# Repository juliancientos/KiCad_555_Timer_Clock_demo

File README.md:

# 555 Timer Clock – 2‑Layer PCB Demonstration (KiCad)

## Overview
This project is a **beginner‑level demonstration of a 2‑layer PCB design** created in **KiCad**, using a simple **555 Timer Clock circuit** as the example.

The primary goal of this project is **to teach and practice basic 2‑layer PCB concepts**, not to create an optimized or production‑ready design. It is intended for students, hobbyists, and beginners learning PCB layout.

---

## Learning Objectives
This project demonstrates:
- Basic **2‑layer PCB layout** (Top & Bottom copper)
- Proper use of **ground planes**
- Via usage between layers
- Simple component placement and routing
- KiCad schematic → PCB workflow

---

## Circuit Description
The circuit is based on a **NE555 Timer IC** configured in **astable mode** to generate a continuous clock signal.

The timing frequency is set by two resistors and one capacitor:

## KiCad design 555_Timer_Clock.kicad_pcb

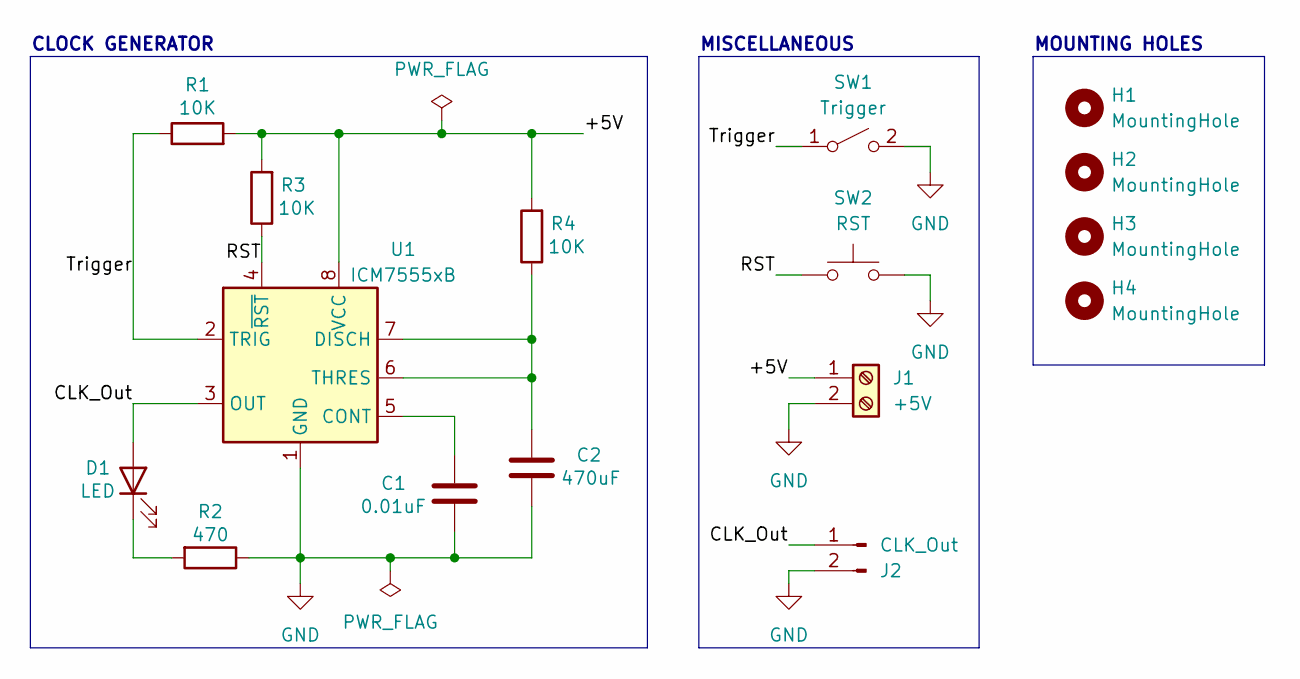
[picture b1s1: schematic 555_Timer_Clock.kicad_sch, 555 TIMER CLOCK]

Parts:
C1: 0.01uF; C_Disc_D3.8mm_W2.6mm_P2.50mm
C2: 470uF; CP_Elec_5x5.4
D1: LED; LED_D5.0mm
H1, H2, H3, H4: MountingHole; MountingHole_2.2mm_M2
J1: +5V; Terminal_Block_5mm
J2: CLK_Out; PinHeader_1x02_P2.54mm_Vertical
R1, R3, R4: 10K; R_1206_3216Metric_Pad1.30x1.75mm_HandSolder
R2: 470; R_1206_3216Metric_Pad1.30x1.75mm_HandSolder
SW1: Trigger; slide_switch_2.54mm
SW2: RST; tact_switch_5mm
U1: ICM7555xB; SOIC-8_3.9x4.9mm_P1.27mm

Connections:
/+5V: J1.1, R1.2, R3.2, R4.2, U1.8 (VCC)
/CLK_Out: D1.2 (A), J2.1, U1.3 (OUT)
/RST: R3.1, SW2.1, U1.4 (~RST)
/Trigger: R1.1, SW1.1 (A), U1.2 (TRIG)
GND: C1.2, C2.2, J1.2, J2.2, R2.1, SW1.2 (B), SW2.2, U1.1 (GND)
unnamed: D1.1 (K), R2.2
unnamed: C1.1, U1.5 (CONT)
unnamed: C2.1, R4.1, U1.6 (THRES), U1.7 (DISCH)

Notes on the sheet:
CLOCK GENERATOR
MOUNTING HOLES
MISCELLANEOUS

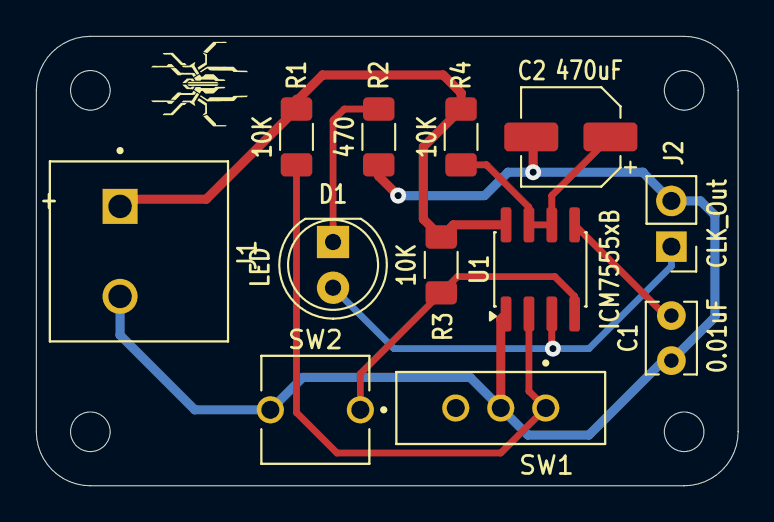
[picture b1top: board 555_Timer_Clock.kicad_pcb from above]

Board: 2 copper layers, 39.0 x 25.0 mm, 16 parts (0 on the bottom side), 8 nets.

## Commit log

2026-04-10 555 Timer Clock Finished Design
